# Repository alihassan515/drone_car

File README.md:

# Hybrid Drone-Car Motherboard Project

Here is the step-by-step design, layout, and optimization process for my dual-mode flying car motherboard.

### 🖼️ Design and Layout Progress Logs

<br>
<br>
<br>
<br>
<br>
<br>
<br>
<br>
<br>
<br>
<br>
<br>
<br>
<br>
<br>
<br>

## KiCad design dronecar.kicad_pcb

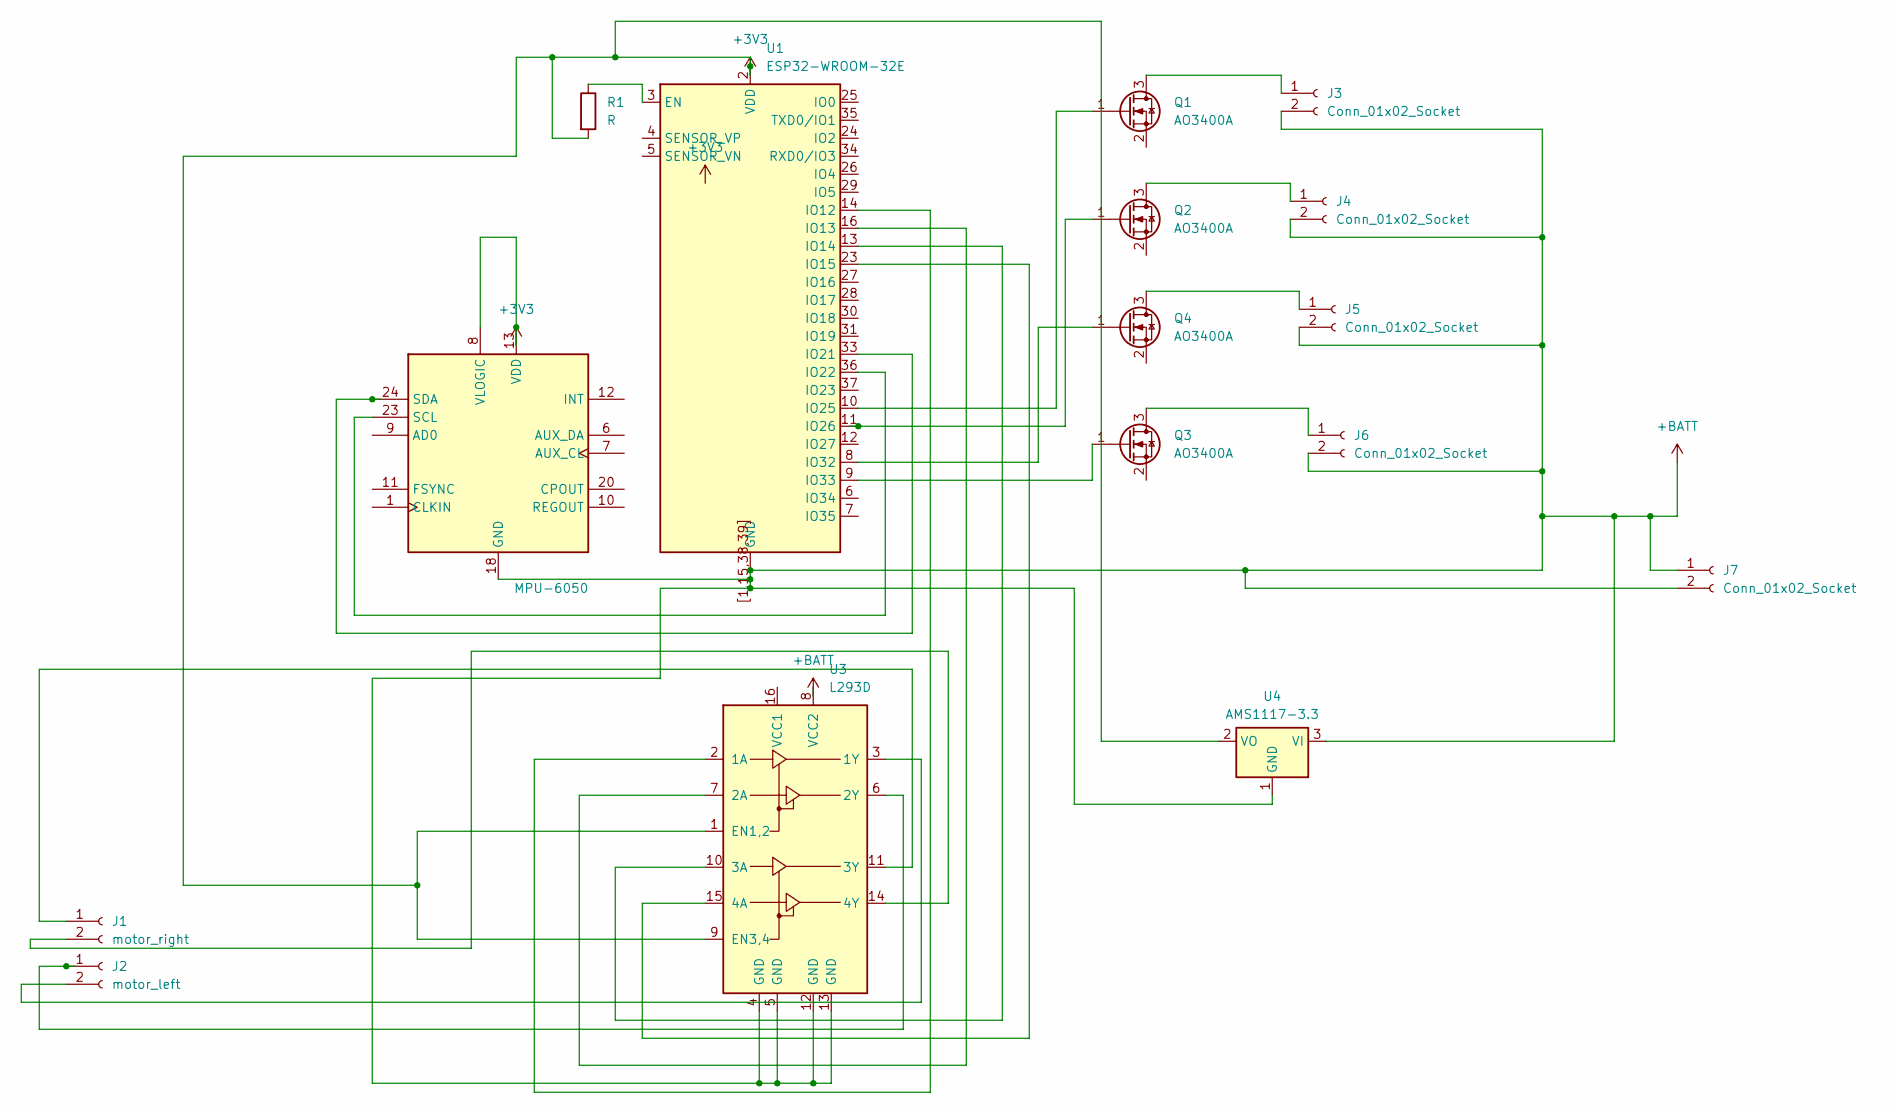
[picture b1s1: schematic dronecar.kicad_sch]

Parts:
J1: motor_right; TerminalBlock_Phoenix_PT-1,5-2-3.5-H_1x02_P3.50mm_Horizontal
J2: motor_left; TerminalBlock_Phoenix_PT-1,5-2-3.5-H_1x02_P3.50mm_Horizontal
J3, J4, J5, J6, J7: Conn_01x02_Socket; TerminalBlock_Phoenix_PT-1,5-2-3.5-H_1x02_P3.50mm_Horizontal
Q1, Q2, Q3, Q4: AO3400A; SOT-23
R1: R; R_Axial_DIN0207_L6.3mm_D2.5mm_P7.62mm_Horizontal
U1: ESP32-WROOM-32E
U2: MPU-6050; InvenSense_QFN-24_4x4mm_P0.5mm
U3: L293D; DIP-16_W7.62mm
U4: AMS1117-3.3; SOT-223-3_TabPin2

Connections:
+3V3: R1.2, U1.2 (VDD), U2.8 (VLOGIC), U2.13 (VDD), U3.1 (EN1,2), U3.9 (EN3,4), U4.2 (VO)
+BATT: J3.2, J4.2, J5.2, J6.2, J7.1, J7.2, U1.1 (GND), U1.15 (GND), U1.38 (GND), U1.39 (GND), U1.[1,15,38,39] (GND), U2.18 (GND), U3.4 (GND), U3.5 (GND), U3.8 (VCC2), U3.12 (GND), U3.13 (GND), U4.1 (GND), U4.3 (VI)
unnamed: J1.1, U3.11 (3Y)
unnamed: J1.2, U3.14 (4Y)
unnamed: J2.1, U3.6 (2Y)
unnamed: J2.2, U3.3 (1Y)
unnamed: J3.1, Q1.3 (D)
unnamed: J4.1, Q2.3 (D)
unnamed: J5.1, Q4.3 (D)
unnamed: J6.1, Q3.3 (D)
unnamed: Q1.1 (G), U1.10 (IO25)
unnamed: Q2.1 (G), U1.11 (IO26)
unnamed: Q3.1 (G), U1.9 (IO33)
unnamed: Q4.1 (G), U1.8 (IO32)
unnamed: R1.1, U1.3 (EN)
unnamed: U1.14 (IO12), U3.2 (1A)
unnamed: U1.16 (IO13), U3.7 (2A)
unnamed: U1.13 (IO14), U3.10 (3A)
unnamed: U1.23 (IO15), U3.15 (4A)
unnamed: U1.33 (IO21), U2.24 (SDA)
unnamed: U1.36 (IO22), U2.23 (SCL)

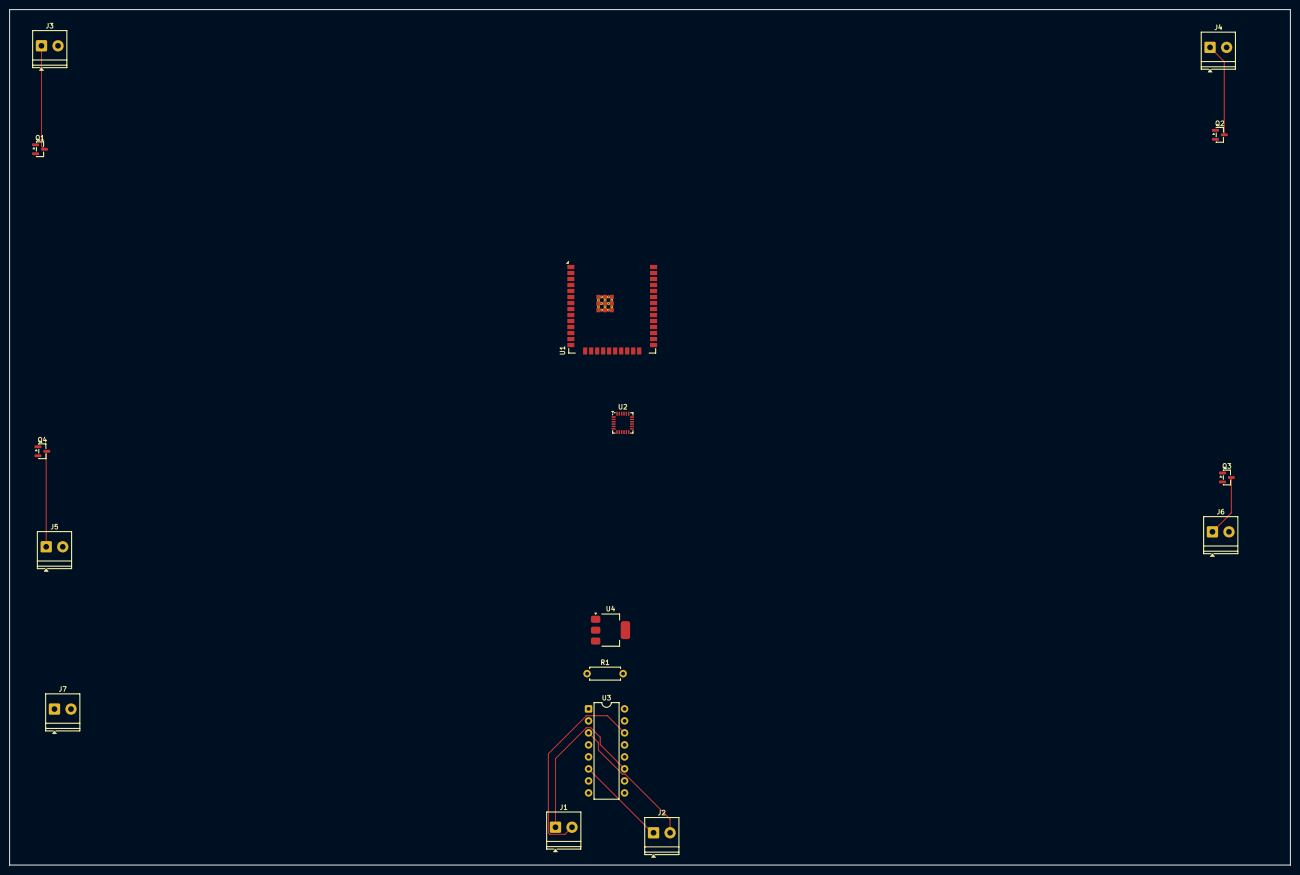
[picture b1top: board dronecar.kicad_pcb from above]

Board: 2 copper layers, 271.0 x 181.0 mm, 16 parts (0 on the bottom side), 21 nets.
